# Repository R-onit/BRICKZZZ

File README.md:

# OLED Breakout Game (ATtiny85)

A minimalistic breakout-style arcade game built on the ATtiny85 microcontroller with an SSD1306 OLED display.

## 🎮 Features
- Ball + Paddle Physics
- Brick Collision Detection
- Button-based Paddle Control
- Sound via Buzzer
- Entirely runs on ATtiny85 (8KB Flash)

## 🛠️ Hardware Used
- ATtiny85 (internal 8MHz)
- SSD1306 OLED 128x64 (I2C)
- Push Buttons
- Active Buzzer
- 3.3V Power Supply (Battery or Regulated)

## 📷 Demo

## Hardware Preview

## 🔌 Wiring
| ATtiny85 Pin | Connected To    |
|--------------|-----------------|
| PB0 (pin 5)  | Button Left     |
| PB1 (pin 6)  | Button Right    |
| PB2 (pin 7)  | OLED SDA        |
| PB4 (pin 3)  | OLED SCL        |
| PB3 (pin 2)  | Buzzer (via 100Ω)|

## Hardware Design
The project now includes a custom-designed PCB made using KiCad. The board integrates the ATtiny85, buzzer, tactile switches, and headers for OLED connection. Schematic, layout, and production-ready files are included in the [`hardware/`](hardware/) folder.

## 📂 Folder Structure
- `attiny_breakout_game.ino` – Main source code
- `font6x8.h` – Font data used for display
- `images/` – Screenshots and wiring diagram
- `hardware/` - Hardware files related to PCB
## 📝 License
MIT License — see LICENSE file.

## 🙋‍♂️ Author
Ronit — [LinkedIn](https://www.linkedin.com/in/ronit-rajendra-patil/) | [GitHub](https://github.com/R-onit/BRICKZZZ/tree/main) |[Youtube](https://youtu.be/keeT_vdv5o0)

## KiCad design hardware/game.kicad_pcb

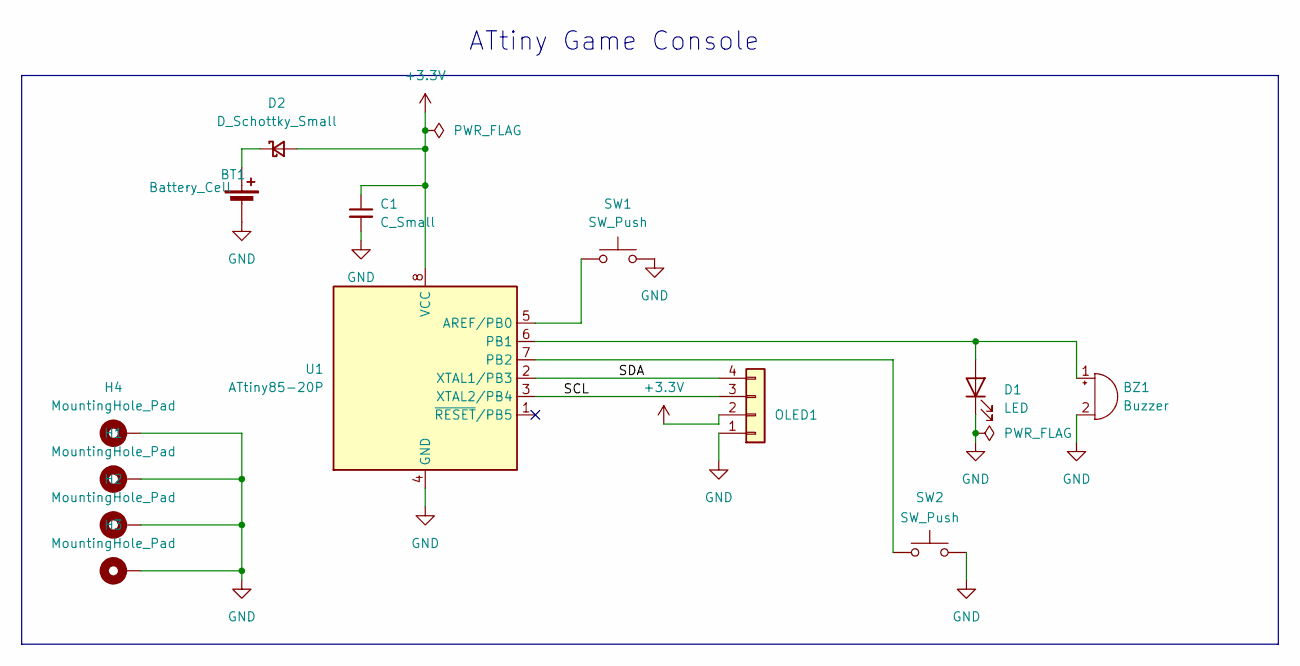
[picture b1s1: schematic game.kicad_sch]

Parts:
BT1: Battery_Cell; BatteryHolder_Keystone_3000_1x12mm
BZ1: Buzzer; MagneticBuzzer_ProSignal_ABT-410-RC
C1: C_Small; C_Disc_D3.0mm_W1.6mm_P2.50mm
D1: LED; LED_D5.0mm
D2: D_Schottky_Small; D_5KPW_P12.70mm_Horizontal
H1, H2, H3, H4: MountingHole_Pad; MountingHole_3.2mm_M3_Pad
OLED1: PinHeader_1x04_P2.54mm_Vertical
SW1, SW2: SW_Push; SW_PUSH_6mm
U1: ATtiny85-20P; DIP-8_W7.62mm

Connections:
+3.3V: C1.1, D2.2 (A), OLED1.2 (VCC), U1.8 (VCC)
/SCL: OLED1.3 (SCL), U1.3 (XTAL2/PB4)
/SDA: OLED1.4 (SDA), U1.2 (XTAL1/PB3)
GND: BT1.2 (-), BZ1.2 (-), C1.2, D1.1 (K), H1.1, H2.1, H3.1, H4.1, OLED1.1 (GND), SW1.2, SW2.2, U1.4 (GND)
unnamed: BT1.1 (+), D2.1 (K)
unnamed: BZ1.1 (+), D1.2 (A), U1.6 (PB1)
unnamed: SW1.1, U1.5 (AREF/PB0)
unnamed: SW2.1, U1.7 (PB2)

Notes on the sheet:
ATtiny Game Console

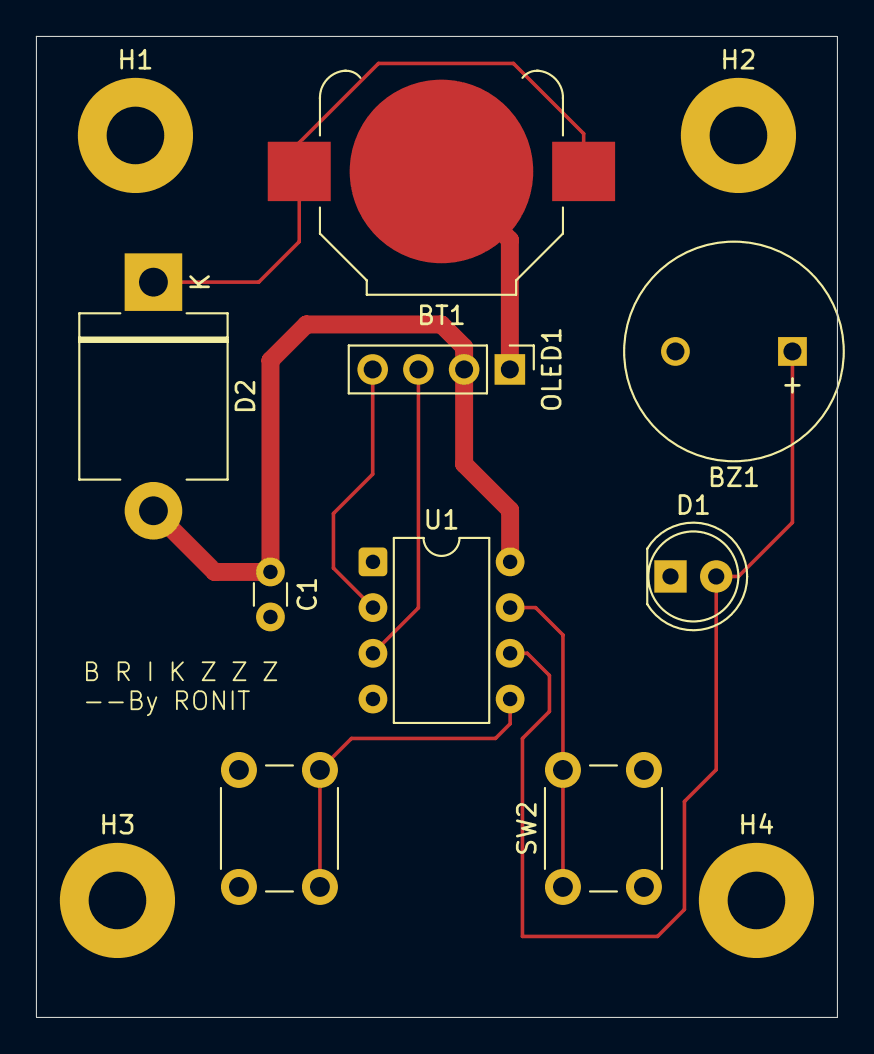
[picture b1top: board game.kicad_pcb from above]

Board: 2 copper layers, 44.5 x 54.5 mm, 13 parts (0 on the bottom side), 8 nets.

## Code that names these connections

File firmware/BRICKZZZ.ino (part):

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// ---------------------	// Vcc,	Pin 1 of SSD1306 Board
// ---------------------	// GND,	Pin 2 of SSD1306 Board
#ifndef SSD1306_SCL
#define SSD1306_SCL		PB4	// SCL,	Pin 3 on SSD1306 Board
#endif
#ifndef SSD1306_SDA
#define SSD1306_SDA		PB3	// SDA,	Pin 4 on SSD1306 Board
#endif
#ifndef SSD1306_SA
#define SSD1306_SA		0x78	// Slave address
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boolean row2[16];
boolean row3[16];
int score = 0; // score - counts the number of blocks hit and resets the array above when devisible by 48(total blocks)
ISR(PCINT0_vect){ // PB0 pin button interrupt			     
   if (player >0){player--;} 
   return;
}
void playerInc(){ // PB2 pin button interrupt
  if (player <128-platformWidth){player++;}
}

void setup() {
  ssd1306_fillscreen(0x00);  // Ensure screen is clean before restarting
  resetGame();
  DDRB = 0b00000010;  	// saet PB1 as output (for the speaker)
  PCMSK = 0b00000001;	// pin change mask: listen to portb bit 1
  GIMSK |= 0b00100000;	// enable PCINT interrupt 
  sei();			// enable all interrupts
  attachInterrupt(0,playerInc,CHANGE);

//EDITED THE ORIGINAL CODE 
  pinMode(PB0, INPUT_PULLUP); // Button 1: use internal pull-up
  pinMode(PB2, INPUT_PULLUP); // Button 2: use internal pull-up

  lastFrame = millis();
}
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
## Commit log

2025-06-12 Initial commit - ATtiny85 breakout game
2025-06-12 second commit - ATtiny85 breakout game
2025-06-12 third commit - added images to the repo
2025-06-12 added PCB Design hardware files
2025-06-12 added PCB Design hardware image files
2025-06-14 did some power routing work
